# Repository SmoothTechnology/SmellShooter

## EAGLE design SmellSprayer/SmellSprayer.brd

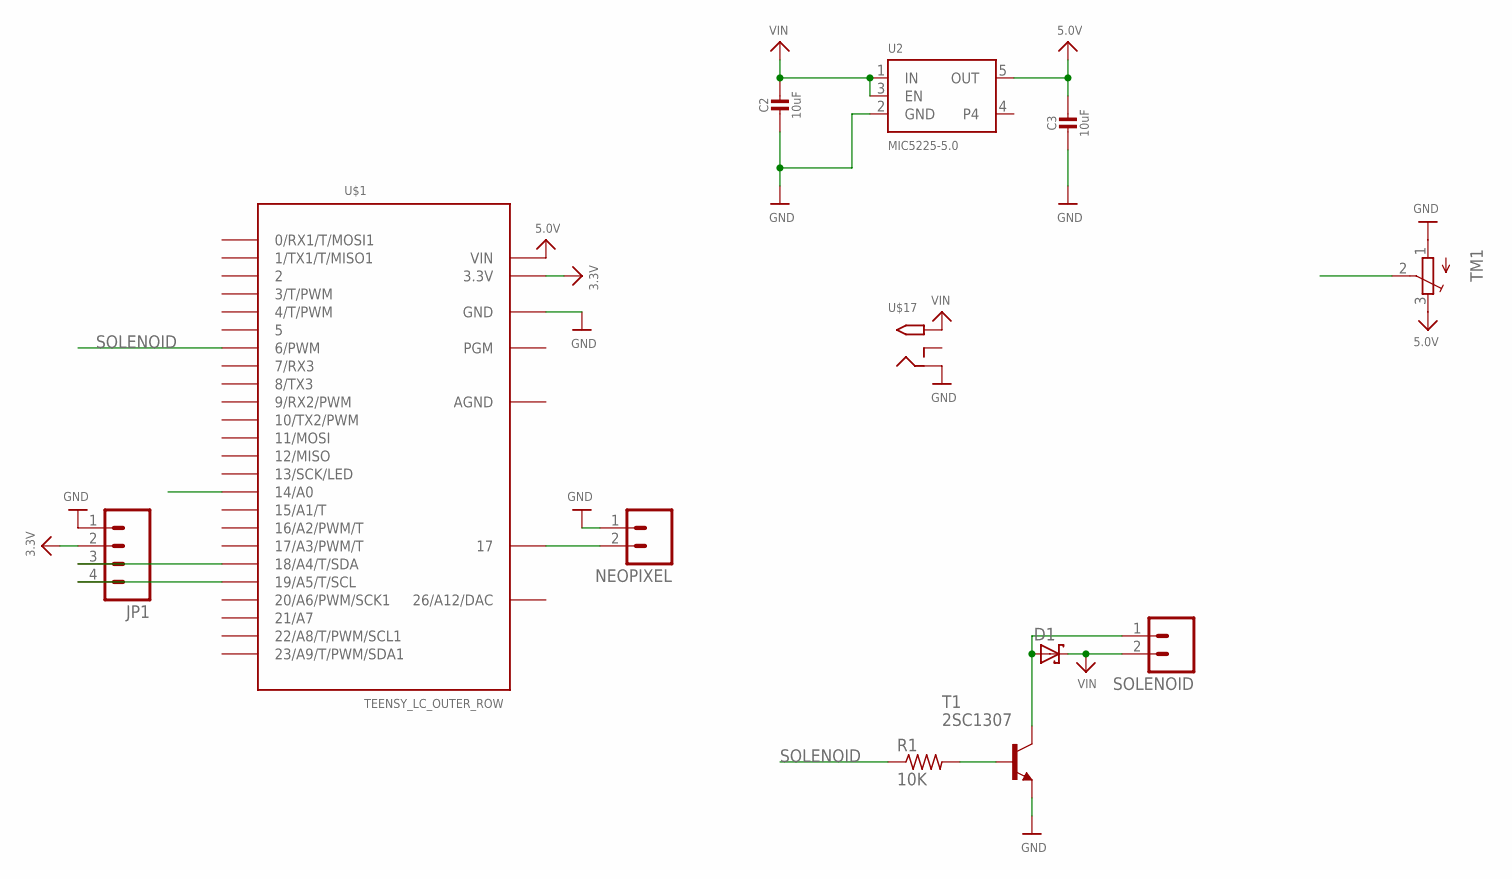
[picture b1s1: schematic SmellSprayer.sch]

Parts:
C2, C3: 10uF; 0805-NO
D1: SCHOTTKY-DIODEDO41-7; DO41-7
JP1: M04POLAR; MOLEX-1X4
NEOPIXEL: M02POLAR; MOLEX-1X2
R1: 10K; R0805
SOLENOID: M023.5MM_LOCK; SCREWTERMINAL-3.5MM-2_LOCK
T1: 2SC1307; TO220AV
TM1: TRIMPOT3386; TRIM-3386
U2: MIC5225-5.0; SOT23-5
U$1: TEENSY_LC_OUTER_ROW; TEENSY3-OUTER_ROW
U$17: 2.1MMJACKSMT; DCJACK_2MM_SMT

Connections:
3.3V: JP1.2, U$1.3.3V, U$1.3.3V1 (3.3V)
5.0V: C3.1, TM1.3 (E), U2.5 (OUT), U$1.VIN
26/A12/DAC: U$1.RESET/DAC (26/A12/DAC)
A0: TM1.2 (S), U$1.14/A0
AGND: U$1.AGND
GND: C2.2, C3.2, JP1.1, NEOPIXEL.1, T1.3 (E), TM1.1 (A), U2.2 (GND), U$1.GND, U$1.GND1 (GND), U$17.GND (RING)
unnamed: D1.A, SOLENOID.1, T1.2 (C)
unnamed: R1.2, T1.1 (B)
unnamed: NEOPIXEL.2, U$1.VBAT (17)
SCL: JP1.4, U$1.19/A5 (19/A5/T/SCL)
SDA: JP1.3, U$1.18/A4 (18/A4/T/SDA)
SOLENOID: R1.1, U$1.6 (6/PWM)
VIN: C2.1, D1.C, SOLENOID.2, U2.1 (IN), U2.3 (EN), U$17.PWR2 (TIP)

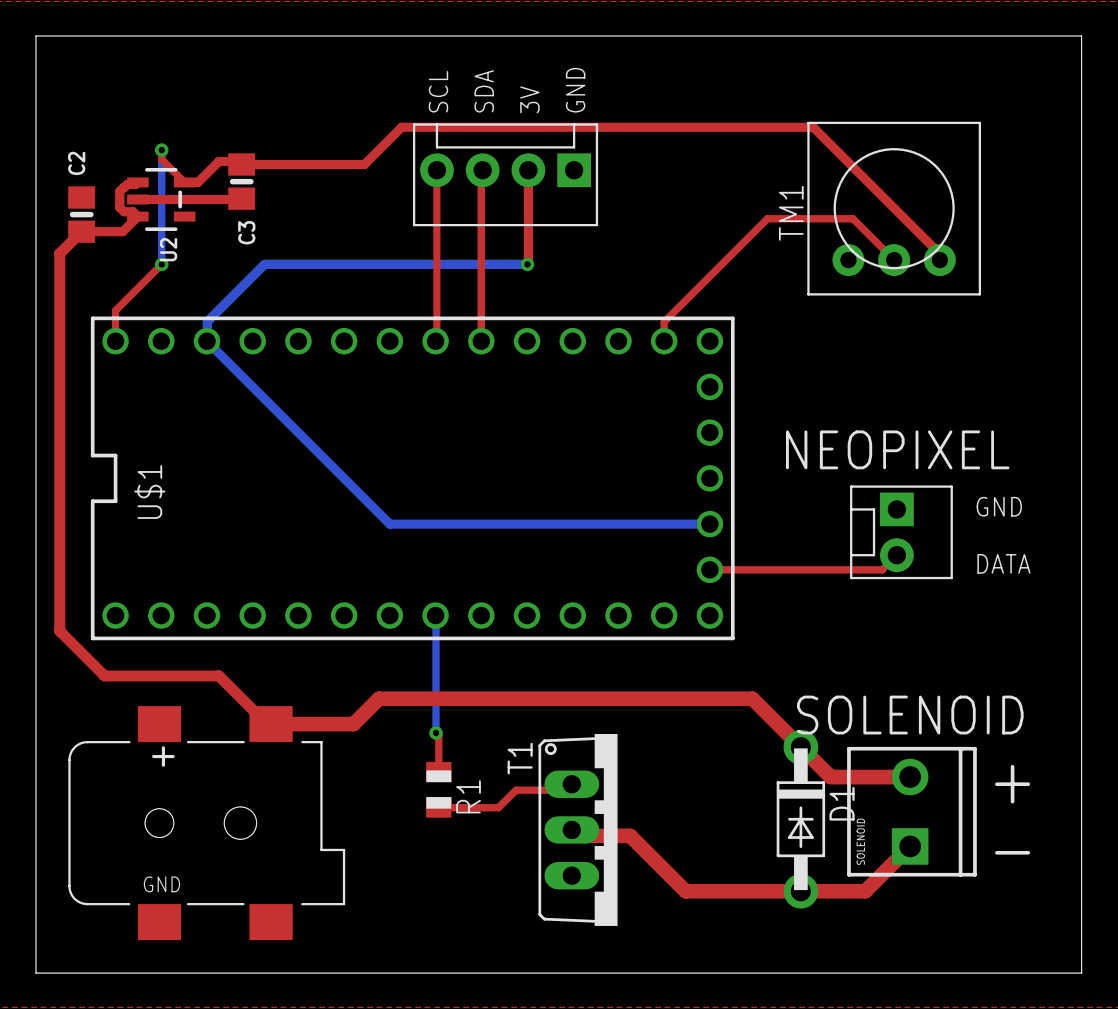
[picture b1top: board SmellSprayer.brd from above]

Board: 2 copper layers, 58.1 x 52.1 mm, 12 parts (0 on the bottom side), 11 nets.

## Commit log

2017-06-15 added board designs
2017-06-28 added working file, DreamMachine
2017-07-12 changed print statements
2017-07-12 Added decrementer
2017-07-12 Added integral pressure drawing
2017-07-12 Sends integral with midi
2017-07-12 Read midi note to flash
2017-07-12 Added clean option code at the top of the code
2017-07-12 Cleaned up more code and removed useless code
2017-07-18 added defines to indicate which teensy/pump ID, removed temperature, sends on different channels
2017-07-18 added .h file to change usb device name
2017-07-26 added LED test (#ifdef TEST_LEDS) and fixed led_height vals
2017-07-29 final panorama sketch
2021-09-14 added all hex files and updated readme

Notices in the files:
parts and their libraries:
microbuilder: This work is placed in the public domain, and may be freely used for commercial and non-commercial work with the following conditions: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
SparkFun-Connectors: Licensing: Creative Commons ShareAlike 4.0 International - https://creativecommons.org/licenses/by-sa/4.0
